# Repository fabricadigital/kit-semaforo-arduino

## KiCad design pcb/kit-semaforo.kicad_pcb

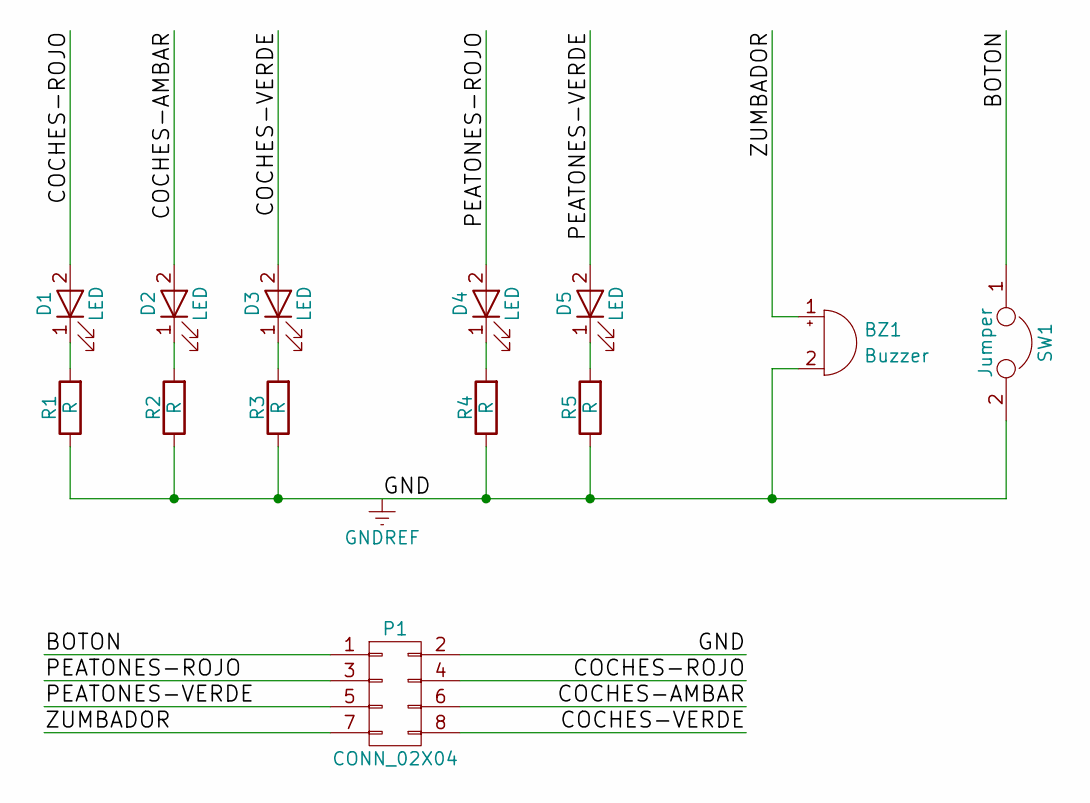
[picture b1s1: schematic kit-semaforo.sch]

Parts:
BZ1: Buzzer; Buzzer_12x9.5RM7.6
D1, D2, D3, D4, D5: LED; LED_5MM_T1-3_4
P1: CONN_02X04; Pin_Header_Straight_2x04_Pitch2.54mm
R1, R2, R3, R4, R5: R; R_Axial_DIN0207_L6.3mm_D2.5mm_P10.16mm_Horizontal
SW1: Jumper; SW_PUSH_6mm

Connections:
/BOTON: P1.1, SW1.1
/COCHES-AMBAR: D2.2 (A), P1.6
/COCHES-ROJO: D1.2 (A), P1.4
/COCHES-VERDE: D3.2 (A), P1.8
/PEATONES-ROJO: D4.2 (A), P1.3
/PEATONES-VERDE: D5.2 (A), P1.5
/ZUMBADOR: BZ1.1 (-), P1.7
GNDREF: BZ1.2 (+), P1.2, R1.1, R2.1, R3.1, R4.1, R5.1, SW1.2
unnamed: D1.1 (K), R1.2
unnamed: D2.1 (K), R2.2
unnamed: D3.1 (K), R3.2
unnamed: D4.1 (K), R4.2
unnamed: D5.1 (K), R5.2

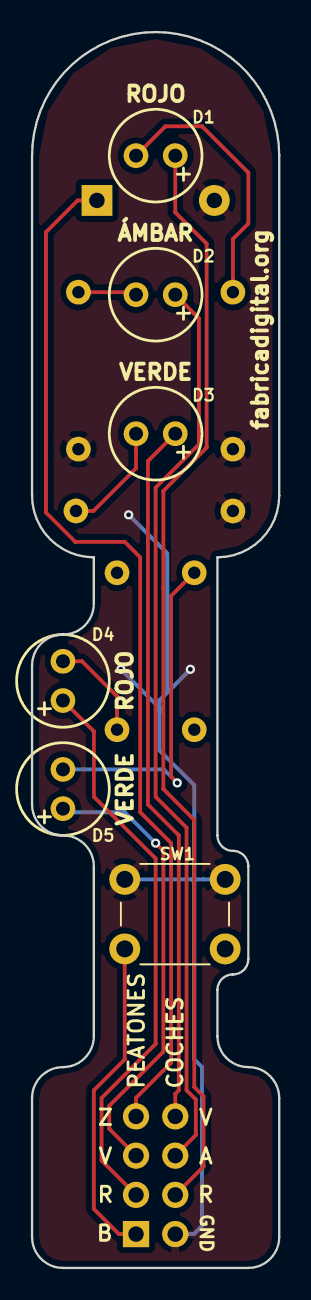
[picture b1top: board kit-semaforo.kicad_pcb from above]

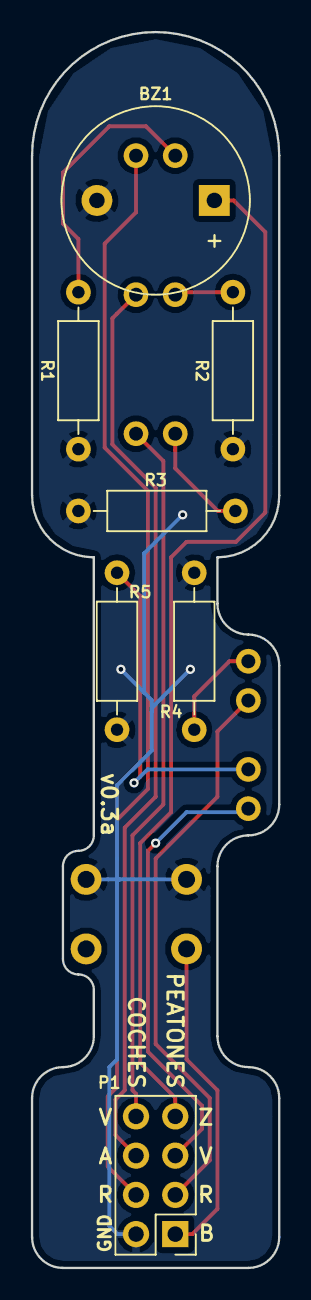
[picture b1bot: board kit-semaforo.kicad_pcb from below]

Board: 2 copper layers, 16.0 x 80.0 mm, 13 parts (7 on the bottom side), 13 nets.

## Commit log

2017-03-24 Commit inicial
2017-04-24 v0.1a enviado a fabricación
2017-05-03 Directorios reestructurados
2017-05-09 Fix: tamaño huella zumbador. Nuevo: Pie ancho.
2017-05-09 README.md añadido
2017-05-09 v0.2a
2017-05-10 Prueba pie del semáforo
2017-06-03 0.3a Añadido botón para peatones
